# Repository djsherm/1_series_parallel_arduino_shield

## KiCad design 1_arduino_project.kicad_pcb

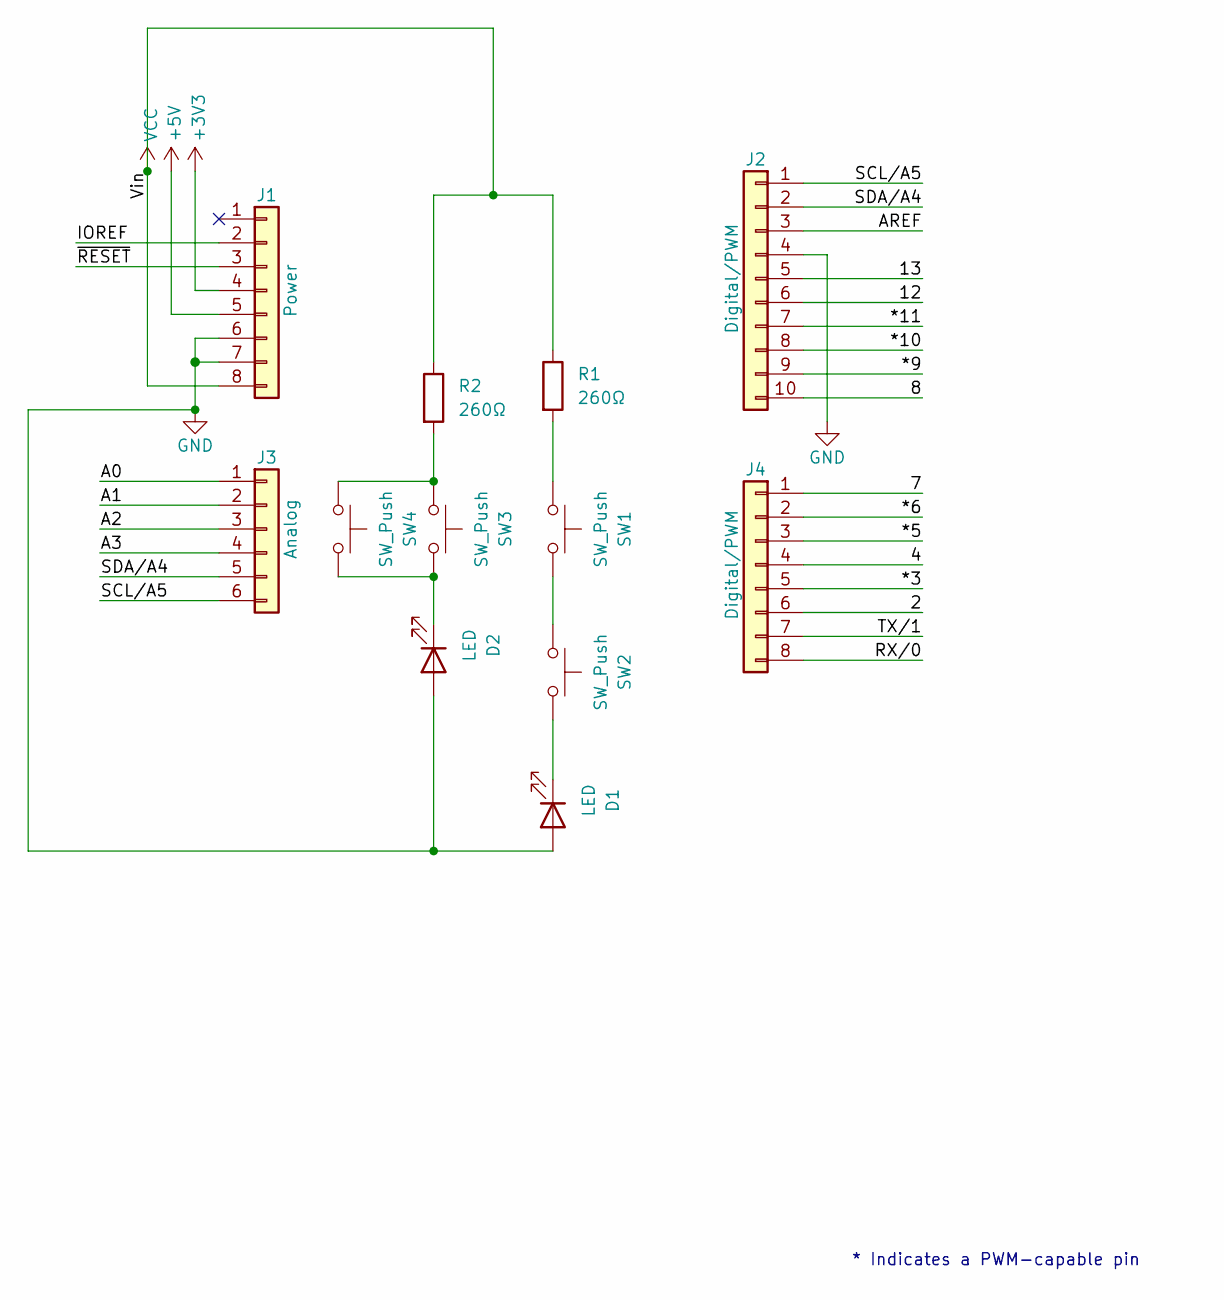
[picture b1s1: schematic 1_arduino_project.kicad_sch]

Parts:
D1, D2: LED; LED_D5.0mm_IRGrey
J1: Power; PinSocket_1x08_P2.54mm_Vertical
J2: Digital/PWM; PinSocket_1x10_P2.54mm_Vertical
J3: Analog; PinSocket_1x06_P2.54mm_Vertical
J4: Digital/PWM; PinSocket_1x08_P2.54mm_Vertical
R1, R2: 260Ω; R_Axial_DIN0207_L6.3mm_D2.5mm_P10.16mm_Horizontal
SW1, SW2, SW3, SW4: SW_Push; TS02 push button

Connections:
+3V3: J1.4
+5V: J1.5
/2: J4.6
/4: J4.4
/7: J4.1
/8: J2.10
/12: J2.6
/13: J2.5
/*3: J4.5
/*5: J4.3
/*6: J4.2
/*9: J2.9
/*10: J2.8
/*11: J2.7
/A0: J3.1
/A1: J3.2
/A2: J3.3
/A3: J3.4
/AREF: J2.3
/IOREF: J1.2
/RX/0: J4.8
/SCL/A5: J2.1, J3.6
/SDA/A4: J2.2, J3.5
/TX/1: J4.7
/~RESET: J1.3
GND: D1.2 (A), D2.2 (A), J1.6, J1.7, J2.4
unnamed: D1.1 (K), SW2.2
unnamed: D2.1 (K), SW3.2, SW4.2
unnamed: R1.2, SW1.1
unnamed: R2.2, SW3.1, SW4.1
unnamed: SW1.2, SW2.1
VCC: J1.8, R1.1, R2.1

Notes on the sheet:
* Indicates a PWM-capable pin

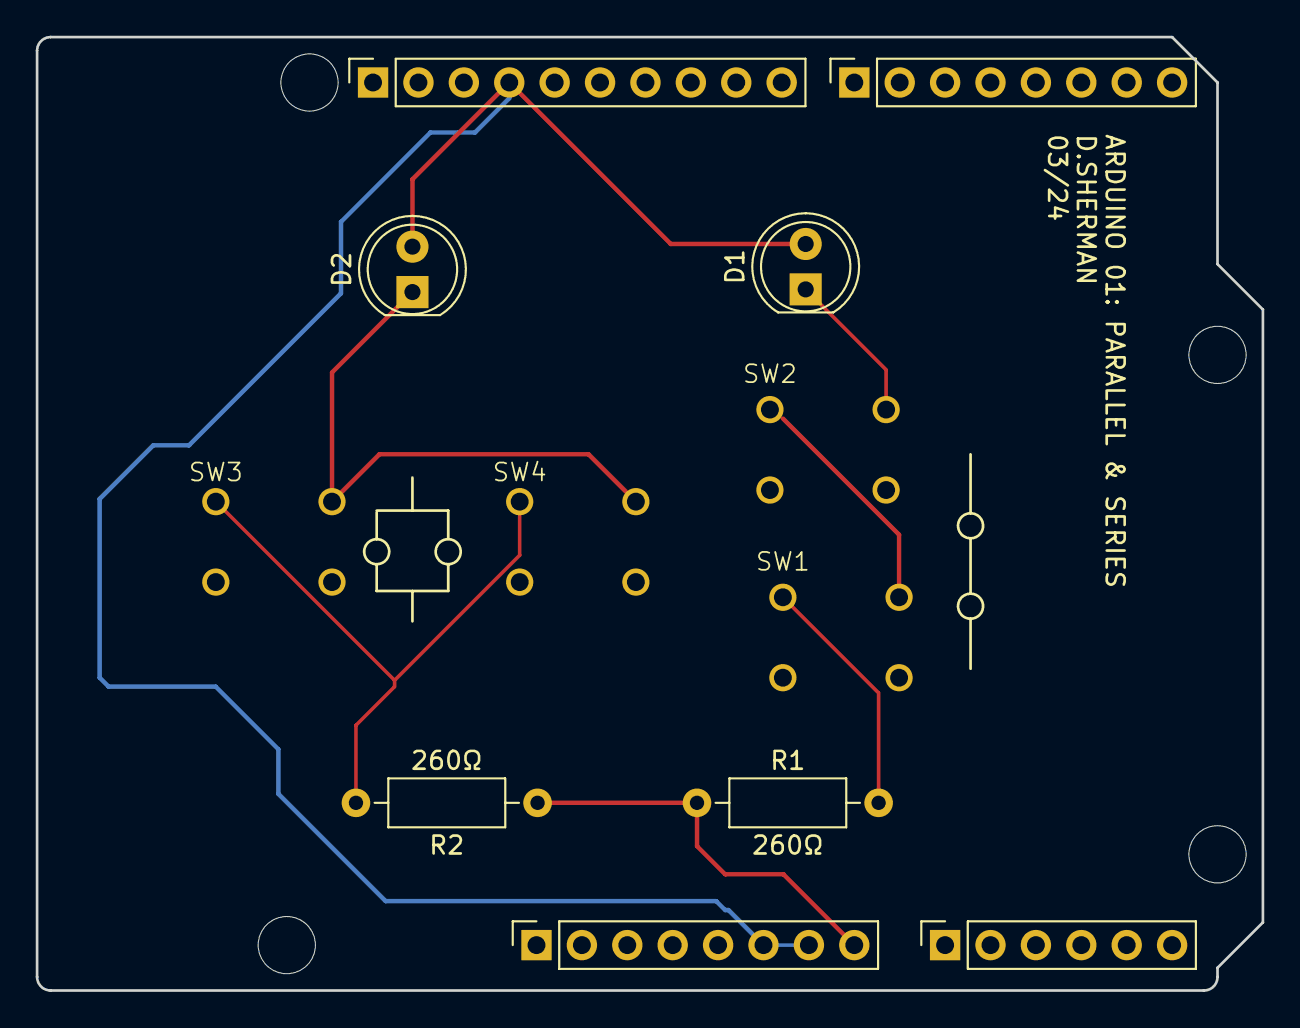
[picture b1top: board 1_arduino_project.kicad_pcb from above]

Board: 2 copper layers, 68.6 x 53.3 mm, 16 parts (0 on the bottom side), 9 nets.

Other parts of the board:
MH1, MH2, MH3, MH4: MountingHole_3.2mm

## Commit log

2024-03-31 added files from KiCad
